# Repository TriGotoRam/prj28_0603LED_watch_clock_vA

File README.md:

Thisis a 0603 SMD Leds watch clock (badge) on STM8L051F3 MCU

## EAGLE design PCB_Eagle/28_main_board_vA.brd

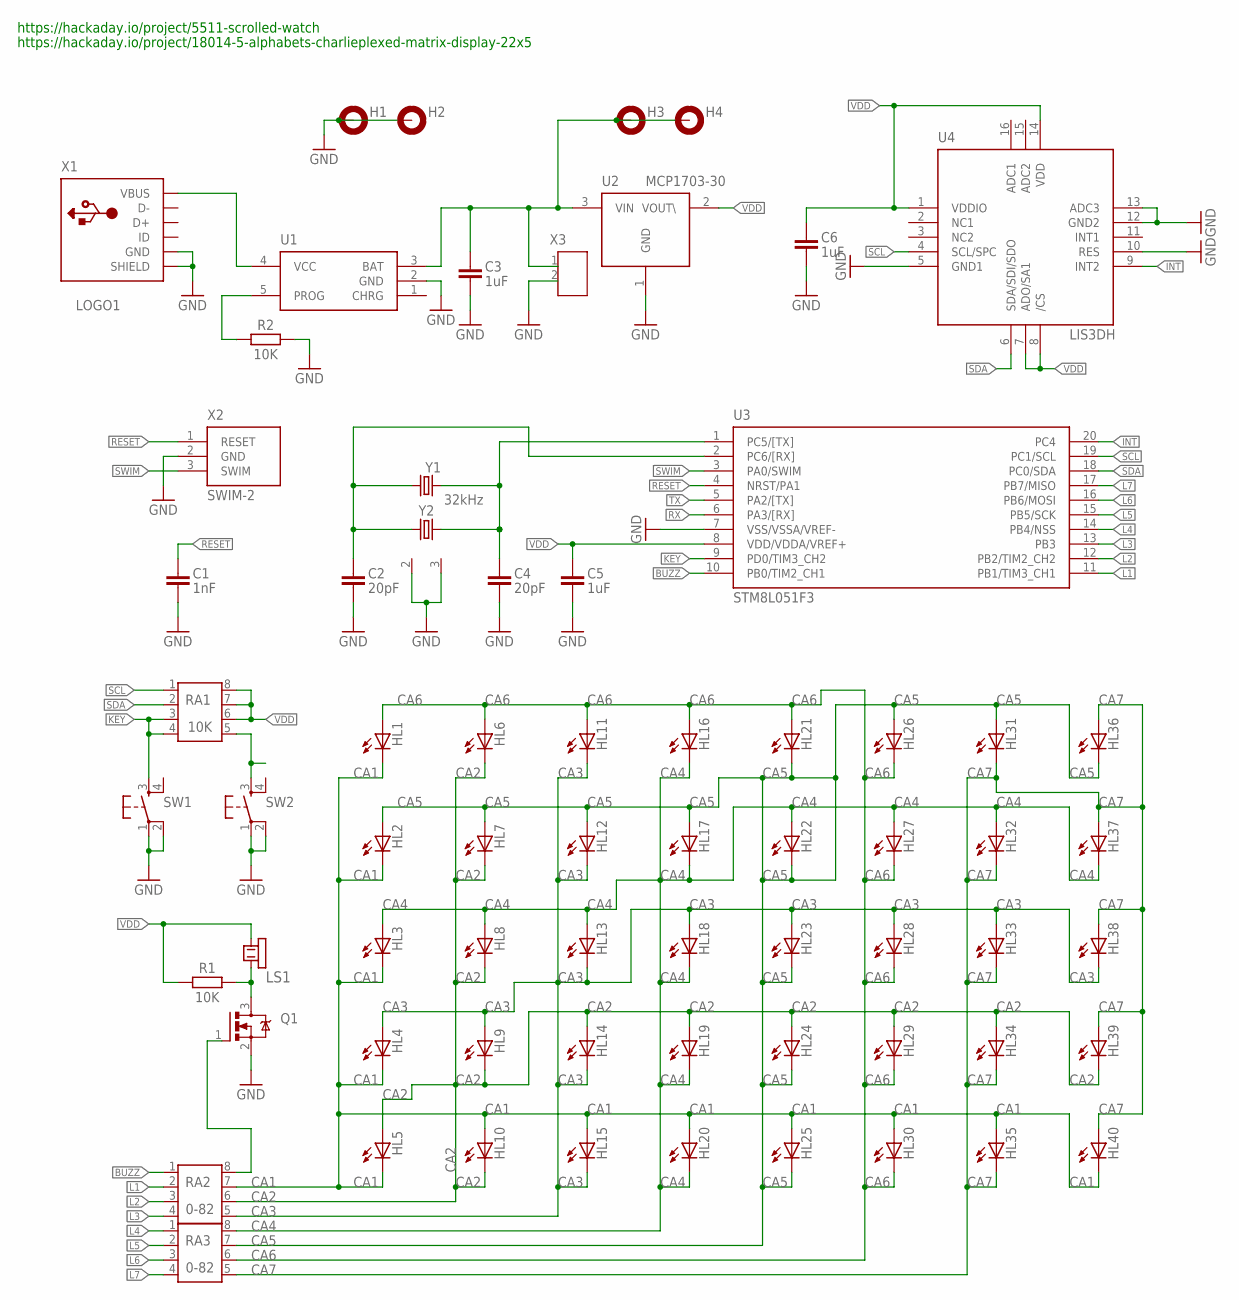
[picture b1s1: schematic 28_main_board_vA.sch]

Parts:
C1: 1nF; C0603
C2, C4: 20pF; C0402
C3, C5, C6: 1uF; C0603
H1, H2, H3, H4: MOUNT-PAD-ROUNDVA; PAD-VA
HL1, HL2, HL3, HL4, HL5, HL6, HL7, HL8, HL9, HL10, HL11, HL12, HL13, HL14, HL15, HL16, HL17, HL18, HL19, HL20, HL21, HL22, HL23, HL24, HL25, HL26, HL27, HL28, HL29, HL30, HL31, HL32, HL33, HL34, HL35, HL36, HL37, HL38, HL39, HL40: LED0603; CHIPLED_0603
LOGO1: LOGO-7; LOGO_OMEGA_COPPER
LS1: BUZZER-PIEZO; BUZZER-PCB-PAD-VA
Q1: FET_NSOT23; SOT23-3-1
R1: 10K; R0603
R2: 10K; R0402
RA1: 10K; EXB38V
RA2, RA3: 0-82; EXB38V
SW1, SW2: SWITCH_G2SM; SW_TACT_SMALL
U1: LTC4054; SOT23-5L
U2: MCP1703-30; SOT23-3
U3: STM8L051F3; TSSOP20
U4: LIS3DH; LGA16
X1: USB-5S-MICRO; USB-B-MICRO-SMD_V03
X2: SWIM-2; ISP-TYPEB-3
X3: CON-2P-1; PLS-2.54-2
Y1: 32kHz; XTAL3215
Y2: REZONATOR-4PIN-SJK-7M; SJK-7M

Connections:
BUZZ: RA2.1, U3.10 (PB0/TIM2_CH1)
CA1: HL1.C, HL2.C, HL3.C, HL4.C, HL5.C, HL10.A, HL15.A, HL20.A, HL25.A, HL30.A, HL35.A, HL40.C, RA2.7
CA2: HL5.A, HL6.C, HL7.C, HL8.C, HL9.C, HL10.C, HL14.A, HL19.A, HL24.A, HL29.A, HL34.A, HL39.C, RA2.6
CA3: HL4.A, HL9.A, HL11.C, HL12.C, HL13.C, HL14.C, HL15.C, HL18.A, HL23.A, HL28.A, HL33.A, HL38.C, RA2.5
CA4: HL3.A, HL8.A, HL13.A, HL16.C, HL17.C, HL18.C, HL19.C, HL20.C, HL22.A, HL27.A, HL32.A, HL37.C, RA3.8
CA5: HL2.A, HL7.A, HL12.A, HL17.A, HL21.C, HL22.C, HL23.C, HL24.C, HL25.C, HL26.A, HL31.A, HL36.C, RA3.7
CA6: HL1.A, HL6.A, HL11.A, HL16.A, HL21.A, HL26.C, HL27.C, HL28.C, HL29.C, HL30.C, RA3.6
CA7: HL31.C, HL32.C, HL33.C, HL34.C, HL35.C, HL36.A, HL37.A, HL38.A, HL39.A, HL40.A, RA3.5
GND: C1.2, C2.2, C3.2, C4.2, C5.2, C6.2, H1.1, H2.1, Q1.2 (S), R2.1, SW1.1, SW1.2 (P1), SW2.1, SW2.2 (P1), U1.2 (GND), U2.1 (GND), U3.7 (VSS/VSSA/VREF-), U4.5 (GND1), U4.10 (RES), U4.12 (GND2), U4.13 (ADC3), X1.GND1 (GND), X1.SHIELD@1 (SHIELD), X1.SHIELD@2 (SHIELD), X1.SHIELD@3 (SHIELD), X1.SHIELD@4 (SHIELD), X1.SHIELD@5 (SHIELD), X2.2 (GND), X3.2, Y2.2 (S), Y2.3 (S)
INT: U3.20 (PC4), U4.9 (INT2)
KEY: RA1.3, RA1.4, SW1.3 (S), U3.9 (PD0/TIM3_CH2)
L1: RA2.2, U3.11 (PB1/TIM3_CH1)
L2: RA2.3, U3.12 (PB2/TIM2_CH2)
L3: RA2.4, U3.13 (PB3)
L4: RA3.1, U3.14 (PB4/NSS)
L5: RA3.2, U3.15 (PB5/SCK)
L6: RA3.3, U3.16 (PB6/MOSI)
L7: RA3.4, U3.17 (PB7/MISO)
unnamed: C4.1, U3.1 (PC5/[TX]), Y1.1, Y2.4 (2)
unnamed: C2.1, U3.2 (PC6/[RX]), Y1.2, Y2.1
unnamed: R2.2, U1.5 (PROG)
unnamed: Q1.1 (G), RA2.8
unnamed: LS1.2, Q1.3 (D), R1.2
unnamed: RA1.5, SW2.3 (S)
RESET: C1.1, U3.4 (NRST/PA1), X2.1 (RESET)
RX: U3.6 (PA3/[RX])
SCL: RA1.1, U3.19 (PC1/SCL), U4.4 (SCL/SPC)
SDA: RA1.2, U3.18 (PC0/SDA), U4.6 (SDA/SDI/SDO)
SWIM: U3.3 (PA0/SWIM), X2.3 (SWIM)
TX: U3.5 (PA2/[TX])
VCC: C3.1, H3.1, H4.1, U1.3 (BAT), U2.3 (VIN), X3.1
VDD: C5.1, C6.1, LS1.1, R1.1, RA1.6, RA1.7, RA1.8, U2.2 (VOUT\), U3.8 (VDD/VDDA/VREF+), U4.1 (VDDIO), U4.7 (ADO/SA1), U4.8 (/CS), U4.14 (VDD)
VUSB: U1.4 (VCC), X1.VBUS1 (VBUS)

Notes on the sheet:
https://hackaday.io/project/5511-scrolled-watch
https://hackaday.io/project/18014-5-alphabets-charlieplexed-matrix-display-22x5

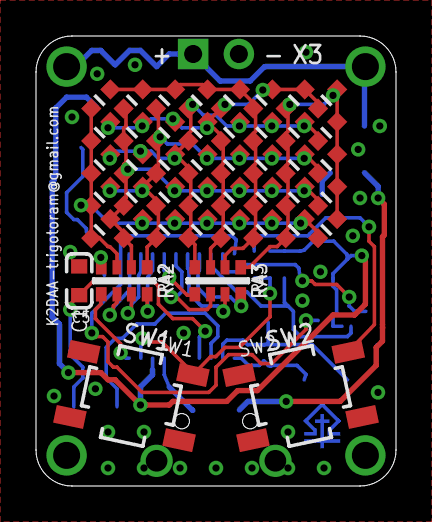
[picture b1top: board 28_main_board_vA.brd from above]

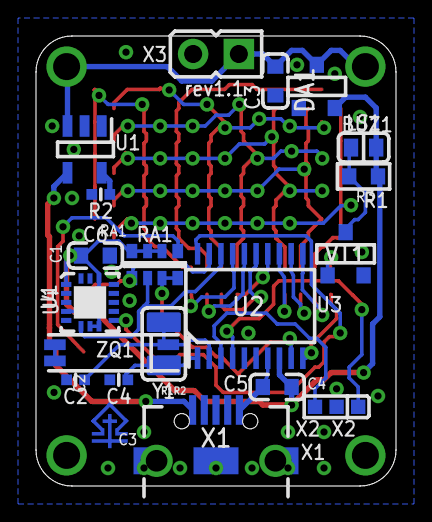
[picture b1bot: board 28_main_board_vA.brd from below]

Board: 2 copper layers, 20.0 x 25.0 mm, 69 parts (20 on the bottom side), 31 nets.
